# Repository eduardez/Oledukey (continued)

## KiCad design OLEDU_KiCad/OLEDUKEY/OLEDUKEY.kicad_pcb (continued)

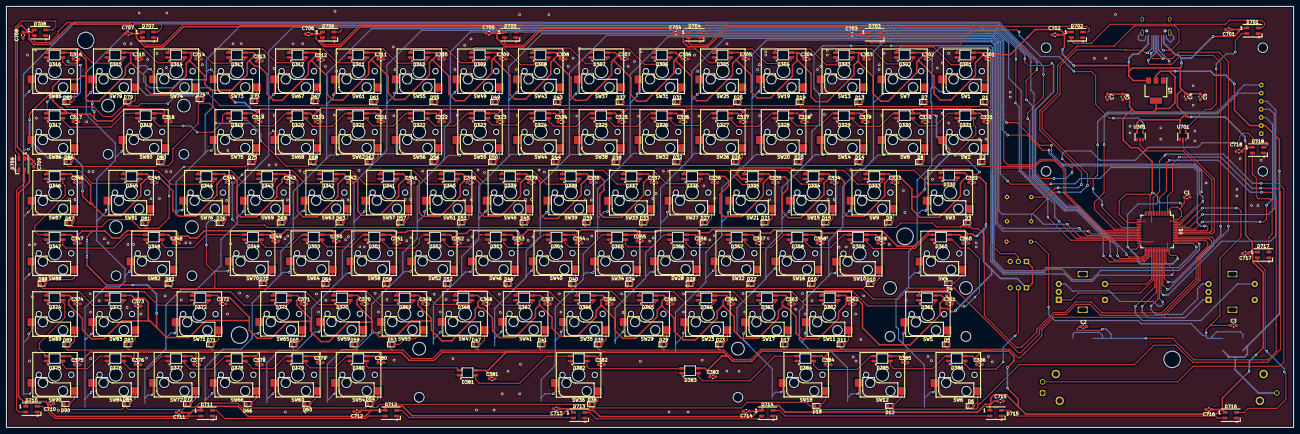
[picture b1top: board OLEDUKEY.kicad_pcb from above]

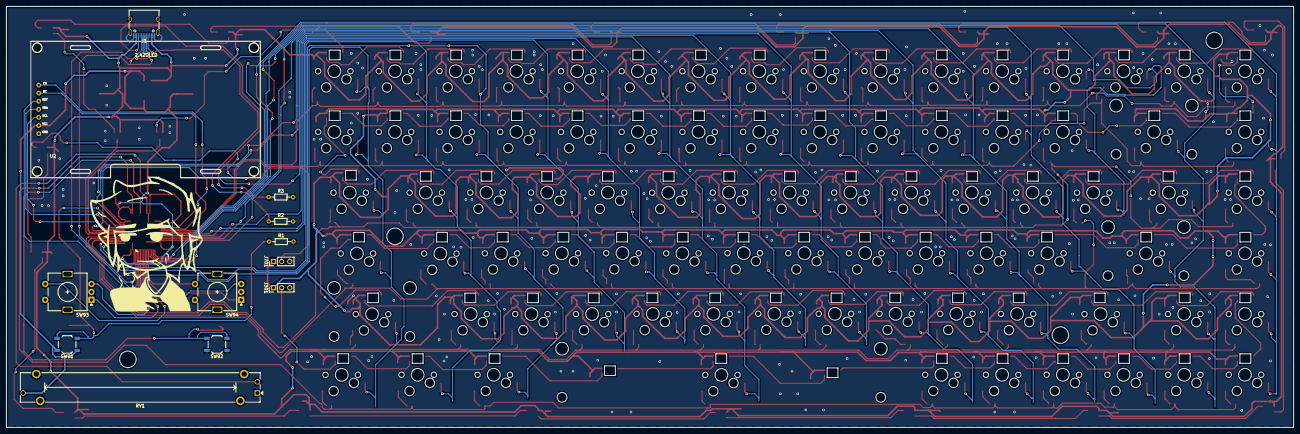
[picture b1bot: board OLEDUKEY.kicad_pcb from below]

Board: 2 copper layers, 403.9 x 132.1 mm, 400 parts (13 on the bottom side), 234 nets.

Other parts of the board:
G007: LOGO; jgfchj77eduardez

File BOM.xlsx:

Comprado | Parte | Valor | Quantity | Total buy | Value/unit | Total Price | Buy | Datasheet
 | Capacitor | 100nF | 109 |  | 2.7000000000000001E-3 | 0.29430000000000001 | https://lcsc.com/product-detail/Multilayer-Ceramic-Capacitor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 | https://datasheet.lcsc.com/lcsc/1809211526_FH-Guangdong-Feng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
 | Capacitor | 10uF | 2 |  | 5.4999999999999997E-3 | 1.0999999999999999E-2 | https://lcsc.com/product-detail/Multilayer-Ceramic-Capacitor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 | https://datasheet.lcsc.com/lcsc/1811021421_Samsung-Electro-M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
 | Diode | 1N4148WS | 84 |  | 1.17E-2 | 0.98280000000000001 | https://lcsc.com/product-detail/Switching-Diode_Shikues-1N41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 | https://datasheet.lcsc.com/lcsc/1811131825_Shikues-1N4148WS_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
 | LED | SK6812MINI | 86 |  | 0.1147 | 9.8642000000000003 | https://es.aliexpress.com/item/32782295214.html | https://cdn-shop.adafruit.com/product-files/2686/SK6812MINI_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
 | LED | SK6812MINI | 18 |  | 0.1099 | 1.9782 | https://es.aliexpress.com/item/32782295214.html | https://cdn-shop.adafruit.com/product-files/2686/SK6812MINI_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
 | Connector | USB_C_TYPE-C-31-M-12 | 1 |  | 0.24529999999999999 | 0.24529999999999999 | https://lcsc.com/product-detail/USB-Connectors_Korean-Hropar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 | https://datasheet.lcsc.com/lcsc/2108131730_Korean-Hroparts-E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
 | Connector | Conn_01x03 | 2 |  | 0 | 0 | Home | ~
 | Resistor | 10k | 1 |  | 0 | 0 | Home | ~
 | Resistor | 5.1k | 2 |  | 0 | 0 | Home | ~
 | Potentiometer slide | R_POT | 1 |  | 11 | 11 | https://es.aliexpress.com/item/4000135544623.html | https://www.mouser.es/datasheet/2/54/pta-778345.pdf
 | Kalih hotswap | Kalih hotswap | 84 |  | 0.1 | 8.4 | https://kbdfans.com/products/mechanical-keyboard-switches-ka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 | ~
 | Stabilizers | Stabilizers | 1 |  | 15.9 | 15.9
 | Gatheron red | SW_Push | 84 |  | 0.2 | 16.8 |  | ~
 | Switch push | SW_Push | 2 |  | 0.3896 | 0.7792 | https://lcsc.com/product-detail/Tactile-Switches_E-Switch-TL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 | https://datasheet.lcsc.com/lcsc/2109061530_E-Switch-TL3342F1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
 | Enconder | Rotary_Encoder_Switch | 2 |  | 0.32 | 0.64 | https://es.aliexpress.com/item/1744383771.html | https://www.farnell.com/datasheets/1837001.pdf
 | Brain | STM32F072RBTx | 1 |  | 12.4 | 12.4 | https://es.aliexpress.com/item/4001114352067.html | http://www.st.com/st-web-ui/static/active/en/resource/techni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
 | OLED | 2.42OLED | 1 |  | 17.77 | 17.77 | https://es.aliexpress.com/item/32965834123.html
 | Volt. Regulator | AMS1117-3.3 | 1 |  | 8.5199999999999998E-2 | 8.5199999999999998E-2 | https://lcsc.com/product-detail/Linear-Voltage-Regulators-LD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 | http://www.advanced-monolithic.com/pdf/ds1117.pdf
 | Buffered driver | 74LVC1G125 | 2 |  | 7.9100000000000004E-2 | 0.15820000000000001 | https://lcsc.com/product-detail/Buffers-Drivers_Texas-Instru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 | https://datasheet.lcsc.com/lcsc/1809200051_Texas-Instruments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
 | PCB | Oledukey | 1 |  | 15.38 | 15.38
 |  |  | Por teclado
 |  | Total | 112.68839999999999

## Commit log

2022-01-08 pcb no copper
2022-01-08 final commit (de momento)
2022-01-08 production files added
2022-01-09 added BOM
